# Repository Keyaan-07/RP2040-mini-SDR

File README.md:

# RP2040 Mini SDR
This is an SDR, as the name says, and it can function in the FM, Airband and NOAA-APT bands ONLY AS A RECEIVER. This is completely legal to make and use.  
I have used RP2040 and ADE-11X+ mixer and SI5351 controllable clock. I thought that i would use a PCB trace USB but then i didn't do it because it would make the board cost go BOOOOM. So, normal USB-A.

I am in no way an RF expert and would love it if someone pointed out my errors and mailed them to [me](mailto:keyaan.1911@gmail.com) or DM on [hackclub](https://hackclub.com) Slack ```@Keyaan```

I think I am gonna make another RF board that could legally transmit too! but that's just an idea for now. 

I am not making a 3D model for this project as i feel this is not required for now. 

## Why I chose to make this project
I have always wanted to try out stuff with RF, especially receiving images from NOAA with my own stuff(I have used [WebSDRs](https://websdr.org) before).  
So i thought that why not make it FM too. And then GPT told me i could legally listen to airband signals too. 

So, i planned to make out an SDR using the goated RP2040 chip and a few mixers and oscillators.  

I have used an SMA connector as it is the most common one i think. 

## How to make and bake it!
Your take the gerber files from this repository and then you upload them to your desired PCB manufacturer. I am using [PCB Power](htttps://pcbpower.com) as they support hcb cards and are only about 350km from my home. and you also order the parts listen in the BOM, i wont order everything, as i have a few things from my previous orders. so, in the BOM, there is Do Not Order column(DNO) that shows what i wont order but you would have to order if you wanna make it. Then you prep the PCB with solder paste. Then you just use the ibom from this repo and place the components and bake it up.

I have set prices to 0 for the components that i have already but i have linked them down.

# Images:

# BOM
|ITEM NAME                 |ITEM PRICE|FUNCTION                                                          |URL                                                                                                                                                        |OTHERS|
|--------------------------|----------|------------------------------------------------------------------|-----------------------------------------------------------------------------------------------------------------------------------------------------------|------|
|PCB Manufacturing(4 Layer)+Stencil|$29.14    |The Main PCB + Stencil                                                     |https://jlcpcb.com                                                                                                                                       |      |                                                               |      |
|PCB Components            |$23.49    |Components on PCB                                                 |https://lcsc.com                                                                                                                                           |      |
|Tape Measure and SMA Cable|$5.57     |tape measure for a dipole antenna and sma to connect it to the PCB|https://www.amazon.in/FREEMANS-IKON-5m-Unbreakable-Bi-material/dp/B010M5GQ78/ , https://www.amazon.in/3AN-Telecom-Coaxial-Extension-Security/dp/B08GKXS915/|      |
|Total                     |$58.20    |                                                                  |                                                                                                                                                           |      |  

### Update 2: i updated the stencil to be ordered from jlcpcb instead of pcbpower, as it was wayy expensive. Thank You.

### Update: I updated the pcb manufacturer from pcbpower to jlcpcb as pcbpower was way too expensive, and i didn't change the stencil if i add stencil on jlcpcb, the stencil+pcb would jump from $15 to $52 because shipping would be so much more, so i will order pcb from jlc for $15 incl. shipping and the stencil from pcbpower only because that would make it overall cheaper. Basically both from jlc would have been $52 and pcb from jlc and stencil form pcbpower is $42, so we save $10.
----
### Note: There are a few resistors and capacitors, which had very high minimum order quantity(MOQ), about 100 pieces so i had to forcefully include those, which i will be utilising in my next highway projects. And tbh the prices were very less(about $0.002 per piece) so i think it is alright.

# PCB Component Breakdown

|Id |Designator                                                           |Designation       |MPN                    |Footprint                          |DNO - Do Not Order|DNP|MOQ|price |Quantity|Amount|LCSC Part No.|Supplier Link                                                                                                                     |
|---|---------------------------------------------------------------------|------------------|-----------------------|-----------------------------------|------------------|---|---|------|--------|------|-------------|----------------------------------------------------------------------------------------------------------------------------------|
|1  |C1, C10, C11, C12, C13, C14, C15, C17, C18, C20, C21, C26, C6, C7, C9|100n              |GRM155R61H104JE14D     |402                                |Yes               |No |-  |0     |15      |0     |             |https://lcsc.com/product-detail/Multilayer-Ceramic-Capacitors-MLCC-SMD-SMT_Murata-Electronics-GRM155R61H104JE14D_C426067.html     |
|2  |C16, C8                                                              |1u                |GRM155R61H105KE05D     |402                                |Yes               |No |-  |0     |2       |0     |             |https://lcsc.com/product-detail/Multilayer-Ceramic-Capacitors-MLCC-SMD-SMT_Murata-Electronics-GRM155R61H105KE05D_C1518208.html    |
|3  |C19, C22, C4, C5                                                     |10u               |CL21A106KBYQNNE        |805                                |No                |No |Yes|0.0509|10      |0.509 |             |https://lcsc.com/product-detail/Multilayer-Ceramic-Capacitors-MLCC-SMD-SMT_Samsung-Electro-Mechanics-CL21A106KBYQNNE_C2932476.html|
|4  |C2, C3                                                               |15p               |GJM1555C1H150FB01D     |402                                |Yes               |No |-  |0     |2       |0     |             |https://lcsc.com/product-detail/Multilayer-Ceramic-Capacitors-MLCC-SMD-SMT_Murata-Electronics-GJM1555C1H150FB01D_C441742.html     |
|5  |C23, C24                                                             |22p               |GJM1555C1H220FB01D     |402                                |No                |No |Yes|0.0379|20      |0.758 |             |https://lcsc.com/product-detail/Multilayer-Ceramic-Capacitors-MLCC-SMD-SMT_Murata-Electronics-GJM1555C1H220FB01D_C882567.html     |
|6  |C25                                                                  |10n               |CC0402JRX7R9BB103      |402                                |No                |No |Yes|0.0016|100     |0.16  |             |https://lcsc.com/product-detail/Multilayer-Ceramic-Capacitors-MLCC-SMD-SMT_YAGEO-CC0402JRX7R9BB103_C272878.html                   |
|7  |D1                                                                   |ESDS314DBVR       |ESDS314DBVR            |ESDS314BVR_SOT95P280X145-5N        |Yes               |No |-  |0     |1       |0     |             |https://lcsc.com/product-detail/ESD-and-Surge-Protection-TVS-ESD_Texas-Instruments-ESDS314DBVR_C1847859.html                      |
|8  |IC1                                                                  |PSA4-5043+        |PSA4-5043+             |PSA45043                           |No                |No |No |2.22  |1       |2.22  |             |https://lcsc.com/product-detail/RF-Amplifiers_Mini-Circuits-PSA4-5043_C5240848.html                                               |
|9  |IC2                                                                  |ADE-11X+          |ADE-11X+               |ADE-11X+_SOTFL254P691X284-6N       |No                |No |No |4.87  |1       |4.87  |             |https://lcsc.com/product-detail/RF-Mixers_Mini-Circuits-ADE-11X_C3176636.html                                                     |
|10 |IC3                                                                  |SI5351A-B-GTR     |SI5351A-B-GTR          |SI5351_SOP50P490X110-10N           |No                |No |No |0.92  |1       |0.92  |             |https://lcsc.com/product-detail/Clock-Generators-PLLs-Frequency-Synthesizers_SKYWORKS-SILICON-LABS-SI5351A-B-GTR_C504891.html     |
|11 |IC4                                                                  |GALI-84+          |GALI-84+               |GALI5                              |No                |No |No |4.3   |1       |4.3   |             |https://lcsc.com/product-detail/RF-Amplifiers_Mini-Circuits-GALI-84_C3193261.html                                                 |
|12 |IC5                                                                  |ADCS7476AIMFX_NOPB|ADCS7476AIMFX_NOPB     |ADCS7476_SOT95P280X145-6N          |No                |No |No |1.9   |1       |1.9   |             |https://lcsc.com/product-detail/Analog-to-Digital-Converters-ADC_Texas-Instruments-ADCS7476AIMFX-NOPB_C91530.html                 |
|13 |J1                                                                   |Conn_Coaxial_Small|BWSMA-KE-P001          |SMA_Amphenol_132289_EdgeMount      |No                |No |No |0.38  |1       |0.38  |             |https://lcsc.com/product-detail/Coaxial-Connectors-RF_BAT-WIRELESS-BWSMA-KE-P001_C496550.html                                     |
|14 |J2                                                                   |USB_A             |USB-212-BCW            |USB_A_Connfly_DS1098_Horizontal    |No                |No |Yes|0.0819|5       |0.4095|             |https://lcsc.com/product-detail/USB-Connectors_XUNPU-USB-212-BCW_C720521.html                                                     |
|15 |L1, L2                                                               |220n              |FEC0805CP-R22G-LRH     |805                                |No                |No |Yes|0.0618|10      |0.618 |             |https://lcsc.com/product-detail/Inductors-SMD_PSA-Prosperity-Dielectrics-FEC0805CP-R22G-LRH_C346387.html                          |
|16 |L3, L4                                                               |15u               |YWLD2012-150K          |805                                |No                |No |Yes|0.0391|10      |0.391 |             |https://lcsc.com/product-detail/Inductors-SMD_YJYCOIN-YWLD2012-150K_C5339219.html                                                 |
|17 |R1, R7                                                               |10k               |RCS040210K0FKED        |402                                |Yes               |No |-  |0     |2       |0     |             |https://lcsc.com/product-detail/Chip-Resistor-Surface-Mount_Vishay-Intertech-RCS040210K0FKED_C3020235.html                        |
|18 |R2, R3                                                               |27                |ERJ2GEJ270X            |402                                |Yes               |No |-  |0     |2       |0     |             |https://lcsc.com/product-detail/Chip-Resistor-Surface-Mount_PANASONIC-ERJ2GEJ270X_C278580.html                                    |
|19 |R4, R5                                                               |1k                |ERJPA2F1001X           |402                                |Yes               |No |-  |0     |2       |0     |             |https://lcsc.com/product-detail/Chip-Resistor-Surface-Mount_PANASONIC-ERJPA2F1001X_C427241.html                                   |
|20 |R6                                                                   |50                |RT0402BRE0750RL        |402                                |No                |No |Yes|0.0207|20      |0.414 |             |https://lcsc.com/product-detail/Chip-Resistor-Surface-Mount_YAGEO-RT0402BRE0750RL_C853312.html                                    |
|21 |SW1                                                                  |SW_Push           |PTS810SJM250SMTRLFS    |SW_SPST_PTS810                     |No                |No |No |0.6   |3       |1.8   |             |https://lcsc.com/product-detail/Tactile-Switches_C-K-PTS810SJM250SMTRLFS_C116501.html                                             |
|22 |U1                                                                   |RP2040            |RP2040                 |QFN-56-1EP_7x7mm_P0.4mm_EP3.2x3.2mm|No                |No |No |1.131 |1       |1.131 |             |https://lcsc.com/product-detail/Microcontrollers-MCU-MPU-SOC_Raspberry-Pi-RP2040_C2040.html                                       |
|23 |U2                                                                   |W25Q128JVS        |W25Q128JVS             |SOIC-8_5.3x5.3mm_P1.27mm           |Yes               |No |-  |0     |1       |0     |             |https://lcsc.com/product-detail/NOR-FLASH_Winbond-Elec-W25Q128JVSIM_C2613930.html                                                 |
|24 |U3                                                                   |AMS1117S-3.3      |AMS1117S-3.3           |SOT-89-3                           |yes               |No |-  |0     |1       |0     |             |https://lcsc.com/product-detail/Voltage-Regulators-Linear-Low-Drop-Out-LDO-Regulators_JSMSEMI-AMS1117S-3-3_C917152.html           |
|25 |Y1                                                                   |Crystal_GND24     |ABM8-272-T3            |Crystal_SMD_3225-4Pin_3.2x2.5mm    |No                |No |No |0.3731|2       |0.7462|             |                                                                                                                                  |
|26 |Y2                                                                   |Crystal_GND24     |XXGBBCNANF-25.000000MHZ|Crystal_SMD_3225-4Pin_3.2x2.5mm    |No                |No |Yes|0.1459|5       |0.7295|             |https://lcsc.com/product-detail/Crystals_TAITIEN-Elec-XXGBBCNANF-25-000000MHZ_C521601.html                                        |
|   |Rounding Errors                                                      |1.2338            |USD                    |                                   |                  |   |   |      |        |      |             |                                                                                                                                  |
|   |Shipping                                                             |3.74              |USD                    |                                   |                  |   |   |      |        |      |             |                                                                                                                                  |
|   |Total                                                                |23.49             |USD                    |                                   |                  |   |   |      |        |      |             |                                                                                                                                  |

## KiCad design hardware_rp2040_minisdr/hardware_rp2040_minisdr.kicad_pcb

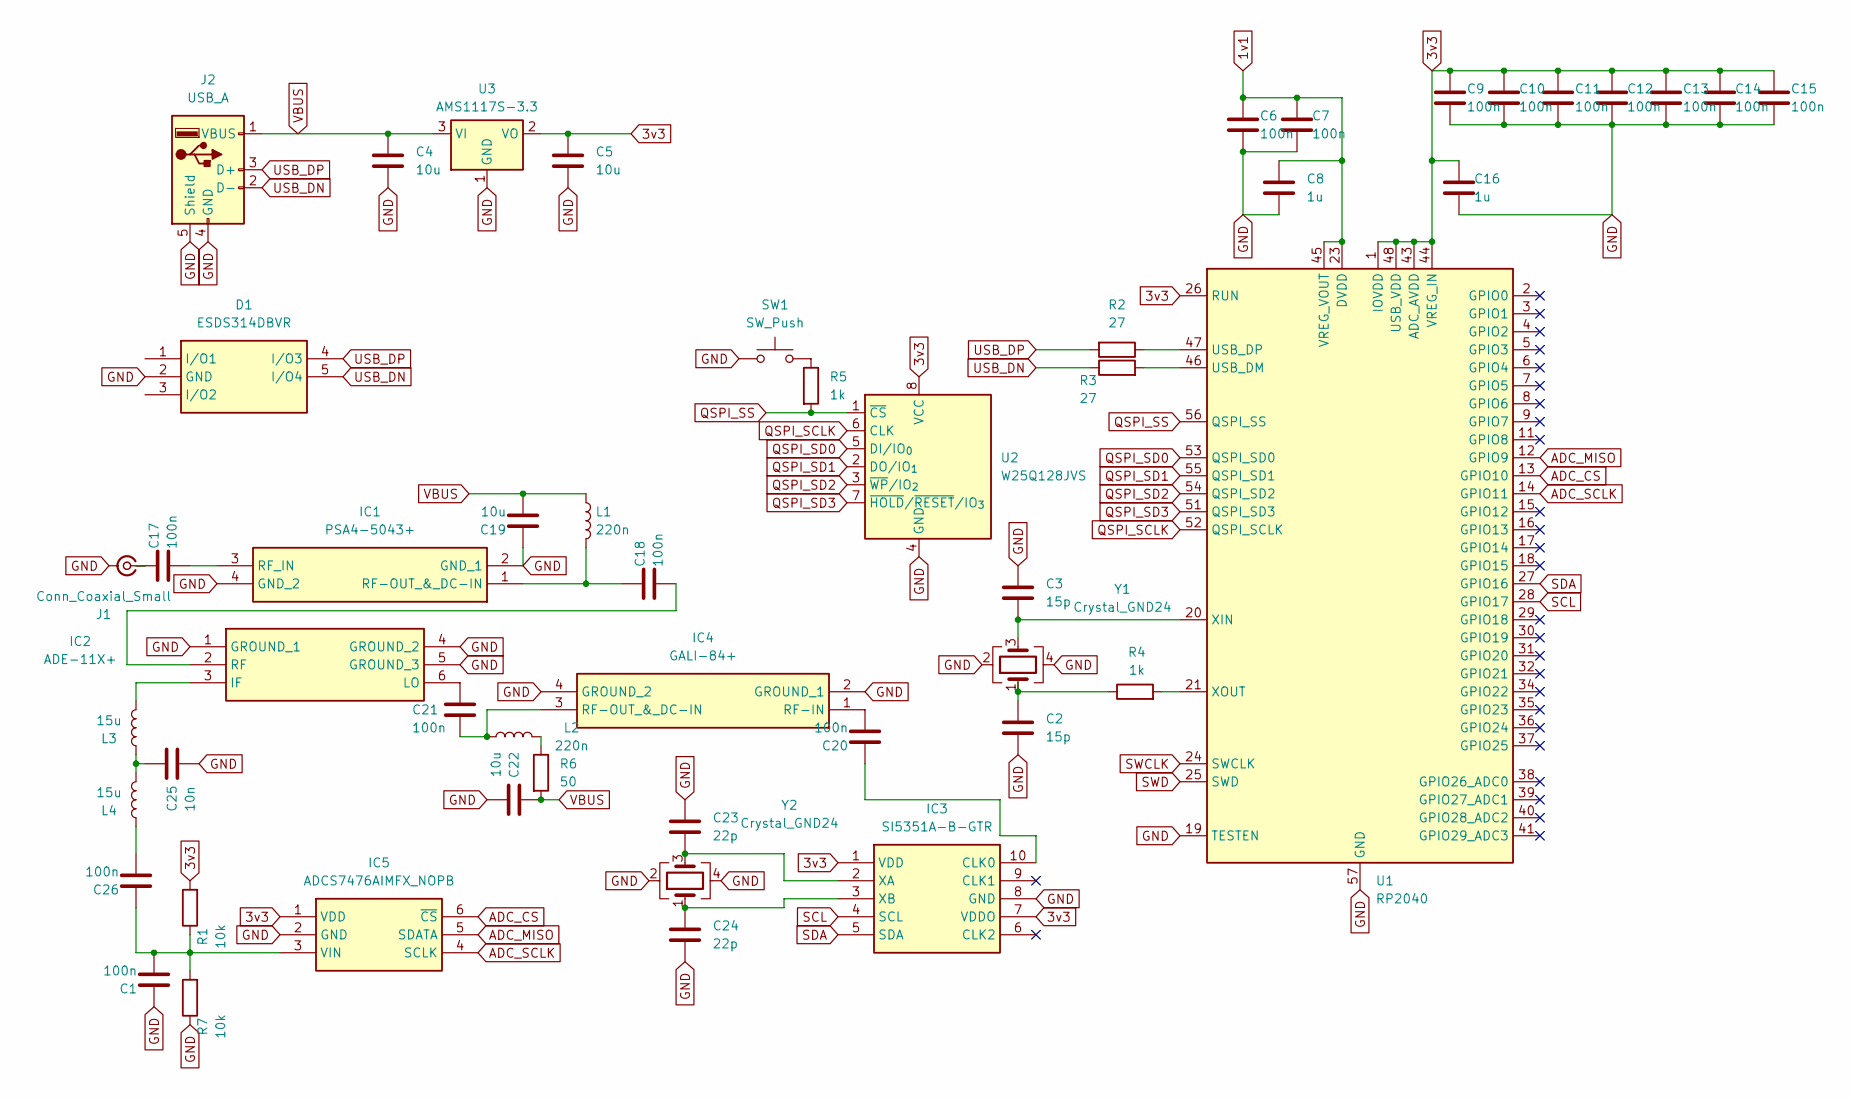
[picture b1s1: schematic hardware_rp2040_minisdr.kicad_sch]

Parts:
C1, C6, C7, C9, C10, C11, C12, C13, C14, C15, C17, C18, C20, C21, C26: 100n; C_0402_1005Metric
C2, C3: 15p; C_0402_1005Metric
C4, C5, C19, C22: 10u; C_0805_2012Metric
C8, C16: 1u; C_0402_1005Metric
C23, C24: 22p; C_0402_1005Metric
C25: 10n; C_0402_1005Metric
D1: ESDS314DBVR; ESDS314BVR_SOT95P280X145-5N; Mouser Part Number 595-ESDS314DBVR
IC1: PSA4-5043+; PSA45043; Mouser Part Number 139-PSA4-5043
IC2: ADE-11X+; ADE-11X+_SOTFL254P691X284-6N; Mouser Part Number 139-ADE-11X
IC3: SI5351A-B-GTR; SI5351_SOP50P490X110-10N; Mouser Part Number 634-SI5351A-B-GTR
IC4: GALI-84+; GALI5; Mouser Part Number 139-GALI-84
IC5: ADCS7476AIMFX_NOPB; ADCS7476_SOT95P280X145-6N; Mouser Part Number 926-ADCS7476AIMFXNPB
J1: Conn_Coaxial_Small; SMA_Amphenol_132289_EdgeMount
J2: USB_A; USB_A_Connfly_DS1098_Horizontal
L1, L2: 220n; L_0805_2012Metric
L3, L4: 15u; L_0805_2012Metric
R1, R7: 10k; R_0402_1005Metric
R2, R3: 27; R_0402_1005Metric
R4, R5: 1k; R_0402_1005Metric
R6: 50; R_0402_1005Metric
SW1: SW_Push; SW_SPST_PTS810
U1: RP2040; QFN-56-1EP_7x7mm_P0.4mm_EP3.2x3.2mm
U2: W25Q128JVS; SOIC-8_5.3x5.3mm_P1.27mm
U3: AMS1117S-3.3; SOT-89-3
Y1, Y2: Crystal_GND24; Crystal_SMD_3225-4Pin_3.2x2.5mm

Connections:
1v1: C6.1, C7.1, C8.1, U1.23 (DVDD), U1.45 (VREG_VOUT), U1.50 (DVDD)
3v3: C5.1, C9.1, C10.1, C11.1, C12.1, C13.1, C14.1, C15.1, C16.1, IC3.1 (VDD), IC3.7 (VDDO), IC5.1 (VDD), R1.2, U1.1 (IOVDD), U1.10 (IOVDD), U1.22 (IOVDD), U1.26 (RUN), U1.33 (IOVDD), U1.42 (IOVDD), U1.43 (ADC_AVDD), U1.44 (VREG_IN), U1.48 (USB_VDD), U1.49 (IOVDD), U2.8 (VCC), U3.2 (VO)
ADC_CS: IC5.6 (~CS), U1.13 (GPIO10)
ADC_MISO: IC5.5 (SDATA), U1.12 (GPIO9)
ADC_SCLK: IC5.4 (SCLK), U1.14 (GPIO11)
GND: C1.1, C2.2, C3.1, C4.2, C5.2, C6.2, C7.2, C8.2, C9.2, C10.2, C11.2, C12.2, C13.2, C14.2, C15.2, C16.2, C19.1, C22.2, C23.1, C24.2, C25.2, D1.2 (GND), IC1.2 (GND_1), IC1.4 (GND_2), IC2.1 (GROUND_1), IC2.4 (GROUND_2), IC2.5 (GROUND_3), IC3.8 (GND), IC4.2 (GROUND_1), IC4.4 (GROUND_2), IC5.2 (GND), J1.2 (Ext), J2.4 (GND), J2.5 (Shield), R7.1, SW1.1, U1.19 (TESTEN), U1.57 (GND), U2.4 (GND), U3.1 (GND), Y1.2, Y1.4, Y2.2, Y2.4
unnamed: C2.1, R4.1, Y1.1
unnamed: C25.1, L3.1, L4.2
unnamed: C26.2, L4.1
unnamed: C18.1, IC1.1 (RF-OUT_&_DC-IN), L1.2
unnamed: C17.2, IC1.3 (RF_IN)
unnamed: IC2.3 (IF), L3.2
unnamed: C21.1, IC2.6 (LO)
unnamed: C18.2, IC2.2 (RF)
unnamed: C20.1, IC3.10 (CLK0)
unnamed: C23.2, IC3.2 (XA), Y2.3
unnamed: C24.1, IC3.3 (XB), Y2.1
unnamed: C20.2, IC4.1 (RF-IN)
unnamed: C21.2, IC4.3 (RF-OUT_&_DC-IN), L2.1
unnamed: C1.2, C26.1, IC5.3 (VIN), R1.1, R7.2
unnamed: C17.1, J1.1 (In)
unnamed: L2.2, R6.1
unnamed: R5.1, SW1.2
unnamed: R3.2, U1.46 (USB_DM)
unnamed: R2.1, U1.47 (USB_DP)
unnamed: C3.2, U1.20 (XIN), Y1.3
unnamed: R4.2, U1.21 (XOUT)
QSPI_SCLK: U1.52 (QSPI_SCLK), U2.6 (CLK)
QSPI_SD0: U1.53 (QSPI_SD0), U2.5 (DI/IO_{0})
QSPI_SD1: U1.55 (QSPI_SD1), U2.2 (DO/IO_{1})
QSPI_SD2: U1.54 (QSPI_SD2), U2.3 (~WP/IO_{2})
QSPI_SD3: U1.51 (QSPI_SD3), U2.7 (~HOLD/~RESET/IO_{3})
QSPI_SS: R5.2, U1.56 (QSPI_SS), U2.1 (~CS)
SCL: IC3.4 (SCL), U1.28 (GPIO17)
SDA: IC3.5 (SDA), U1.27 (GPIO16)
SWCLK: U1.24 (SWCLK)
SWD: U1.25 (SWD)
USB_DN: D1.5 (I/O4), J2.2 (D-), R3.1
USB_DP: D1.4 (I/O3), J2.3 (D+), R2.2
VBUS: C4.1, C19.2, C22.1, J2.1 (VBUS), L1.1, R6.2, U3.3 (VI)

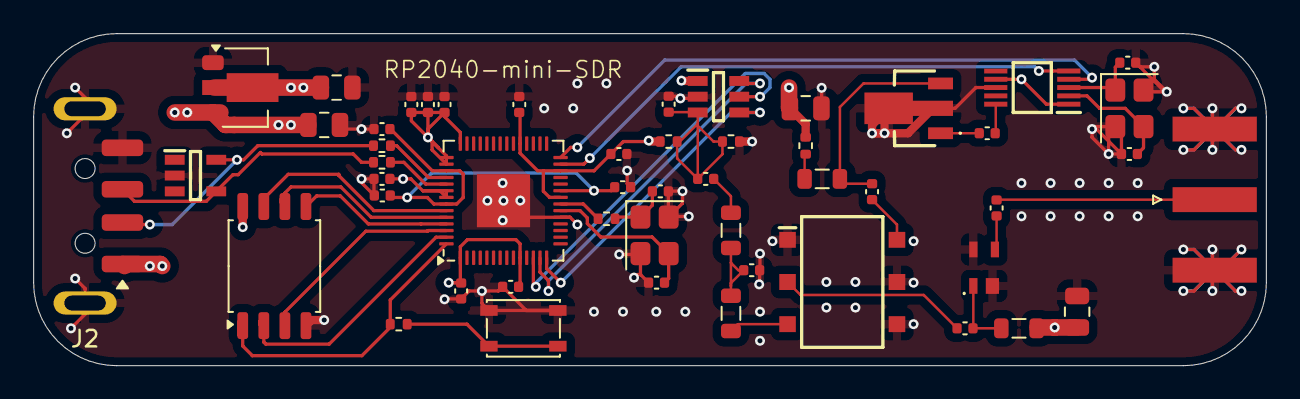
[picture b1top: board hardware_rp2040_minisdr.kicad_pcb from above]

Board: 4 copper layers, 74.2 x 20.0 mm, 51 parts (0 on the bottom side), 38 nets.

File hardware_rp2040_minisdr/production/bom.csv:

Designator,Footprint,Quantity,Value,LCSC Part #
"C1, C10, C11, C12, C13, C14, C15, C17, C18, C20, C21, C26, C6, C7, C9",0402,15,100n,
"C16, C8",0402,2,1u,
"C19, C22, C4, C5",0805,4,10u,
"C2, C3",0402,2,15p,
"C23, C24",0402,2,22p,
C25,0402,1,10n,
D1,ESDS314BVR_SOT95P280X145-5N,1,ESDS314DBVR,
IC1,PSA45043,1,PSA4-5043+,
IC2,ADE-11X+_SOTFL254P691X284-6N,1,ADE-11X+,
IC3,SI5351_SOP50P490X110-10N,1,SI5351A-B-GTR,
IC4,GALI5,1,GALI-84+,
IC5,ADCS7476_SOT95P280X145-6N,1,ADCS7476AIMFX_NOPB,
J1,SMA_Amphenol_132289_EdgeMount,1,Conn_Coaxial_Small,
J2,USB_A_Connfly_DS1098_Horizontal,1,USB_A,
"L1, L2",0805,2,220n,
"L3, L4",0805,2,15u,
"R1, R7",0402,2,10k,
"R2, R3",0402,2,27,
"R4, R5",0402,2,1k,
R6,0402,1,50,
SW1,SW_SPST_PTS810,1,SW_Push,
U1,QFN-56-1EP_7x7mm_P0.4mm_EP3.2x3.2mm,1,RP2040,
U2,SOIC-8_5.3x5.3mm_P1.27mm,1,W25Q128JVS,
U3,SOT-89-3,1,AMS1117S-3.3,
"Y1, Y2",Crystal_SMD_3225-4Pin_3.2x2.5mm,2,Crystal_GND24,

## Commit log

2025-06-16 Block Diagram
2025-06-18 Image Fix
2025-06-18 Hardware Files
2025-06-18 Components
2025-06-18 New Block Diagram
2025-06-22 update time
2025-06-22 Parts
2025-06-22 add bd
2025-06-22 time spent
2025-06-22 started with schematic
2025-06-22 schematic
2025-06-22 time
2025-06-22 journal
2025-06-22 typo
2025-06-22 crystal(not meth)
2025-06-22 update journal
2025-06-23 new day
2025-06-23 board
2025-06-23 journaling
2025-06-23 usb-fail
2025-06-23 LEDs
2025-06-23 explanation
2025-06-23 final schematic
2025-06-24 laptop in schooool
2025-06-24 pcb placement
2025-06-24 image
2025-06-24 pcb final inage on 24 june
2025-06-25 journalinggggggggg
2025-06-25 pcb journal
2025-06-25 mistake
2025-06-25 pcb readyyy
2025-06-25 final look
2025-06-25 pcb hardware!
2025-06-26 change in VBUS connection
2025-06-26 final pcb probably journaling
2025-06-26 pcb final i think
2025-06-26 readme
2025-06-26 no 3d model
2025-06-26 README.md
2025-06-26 Images
2025-06-27 silkscreen stuff
2025-06-27 silkscreen designs
2025-06-27 update pic in journal
2025-06-27 production files update
2025-06-27 ibom.html update
2025-06-27 added Do not touch in silkscreen
2025-06-27 DRC check done!
2025-06-27 pcb stencil output generated
2025-06-27 BOM - WIP
2025-06-27 Upload Files
2025-06-27 pcb doneeee
2025-06-27 Added Total Cost
2025-06-27 Update total prices
2025-06-27 Fix typo
2025-06-27 Create LICENSE
2025-06-29 update costs
2025-06-29 BOM updated
2025-07-03 no changes
2025-07-03 BOM optimised
2025-07-16 'journaling'
